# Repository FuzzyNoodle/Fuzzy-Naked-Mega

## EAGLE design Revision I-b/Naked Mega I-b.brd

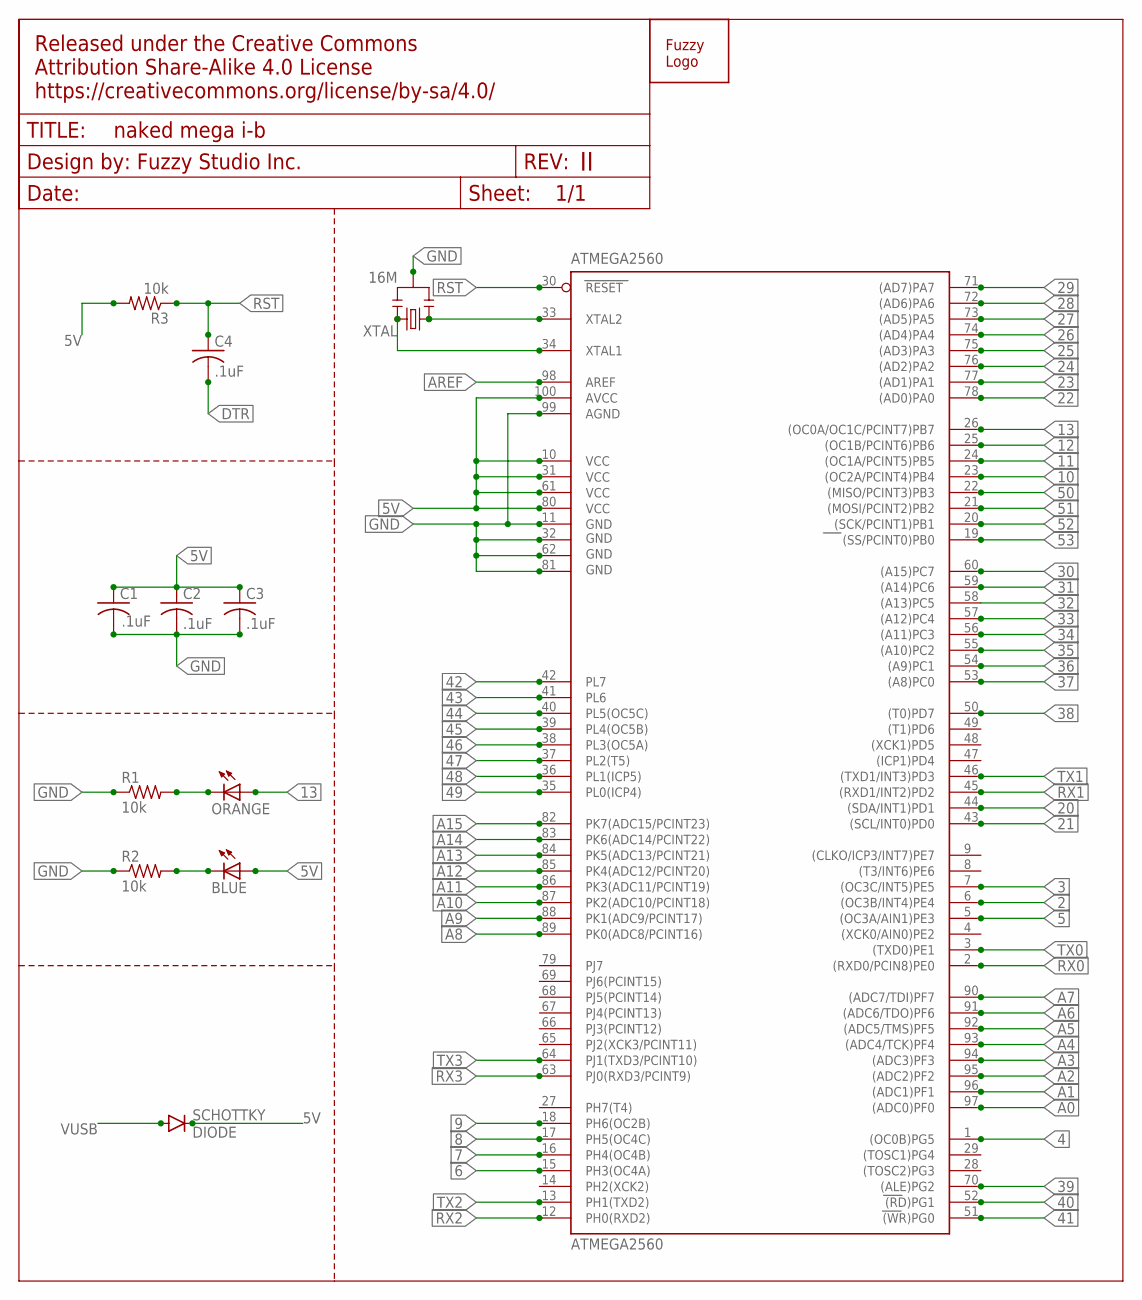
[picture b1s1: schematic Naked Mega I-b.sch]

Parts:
ATMEGA2560: ATMEGA2560; TQFP100
BLUE: L; SMD-0805-LED
C1: CAPACITOR-SMD-0805; SMD-0805
C2, C3, C4: .1uF; SMD-0805
ORANGE: L; SMD-0805-LED
R1, R2, R3: 10k; SMD-0805
SCHOTTKY: DIODE; SOD-323
U$1: LOGO; LOGO-S
U$3: DOCFRAME; CREATIVECOMMONS
XTAL: 16M; RESONATOR

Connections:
2: ATMEGA2560.6 ((OC3B/INT4)PE4)
3: ATMEGA2560.7 ((OC3C/INT5)PE5)
4: ATMEGA2560.1 ((OC0B)PG5)
5: ATMEGA2560.5 ((OC3A/AIN1)PE3)
5V: ATMEGA2560.10 (VCC), ATMEGA2560.31 (VCC1), ATMEGA2560.61 (VCC2), ATMEGA2560.80 (VCC3), ATMEGA2560.100 (AVCC), BLUE.1 (A), C1.1, C2.1, C3.1, R3.2, SCHOTTKY.C
6: ATMEGA2560.15 (PH3(OC4A))
7: ATMEGA2560.16 (PH4(OC4B))
8: ATMEGA2560.17 (PH5(OC4C))
9: ATMEGA2560.18 (PH6(OC2B))
10: ATMEGA2560.23 ((OC2A/PCINT4)PB4)
11: ATMEGA2560.24 ((OC1A/PCINT5)PB5)
12: ATMEGA2560.25 ((OC1B/PCINT6)PB6)
13: ATMEGA2560.26 ((OC0A/OC1C/PCINT7)PB7), ORANGE.1 (A)
20: ATMEGA2560.44 ((SDA/INT1)PD1)
21: ATMEGA2560.43 ((SCL/INT0)PD0)
22: ATMEGA2560.78 ((AD0)PA0)
23: ATMEGA2560.77 ((AD1)PA1)
24: ATMEGA2560.76 ((AD2)PA2)
25: ATMEGA2560.75 ((AD3)PA3)
26: ATMEGA2560.74 ((AD4)PA4)
27: ATMEGA2560.73 ((AD5)PA5)
28: ATMEGA2560.72 ((AD6)PA6)
29: ATMEGA2560.71 ((AD7)PA7)
30: ATMEGA2560.60 ((A15)PC7)
31: ATMEGA2560.59 ((A14)PC6)
32: ATMEGA2560.58 ((A13)PC5)
33: ATMEGA2560.57 ((A12)PC4)
34: ATMEGA2560.56 ((A11)PC3)
35: ATMEGA2560.55 ((A10)PC2)
36: ATMEGA2560.54 ((A9)PC1)
37: ATMEGA2560.53 ((A8)PC0)
38: ATMEGA2560.50 ((T0)PD7)
39: ATMEGA2560.70 ((ALE)PG2)
40: ATMEGA2560.52 ((RD)PG1)
41: ATMEGA2560.51 ((WR)PG0)
42: ATMEGA2560.42 (PL7)
43: ATMEGA2560.41 (PL6)
44: ATMEGA2560.40 (PL5(OC5C))
45: ATMEGA2560.39 (PL4(OC5B))
46: ATMEGA2560.38 (PL3(OC5A))
47: ATMEGA2560.37 (PL2(T5))
48: ATMEGA2560.36 (PL1(ICP5))
49: ATMEGA2560.35 (PL0(ICP4))
50: ATMEGA2560.22 ((MISO/PCINT3)PB3)
51: ATMEGA2560.21 ((MOSI/PCINT2)PB2)
52: ATMEGA2560.20 ((SCK/PCINT1)PB1)
53: ATMEGA2560.19 ((SS/PCINT0)PB0)
A0: ATMEGA2560.97 ((ADC0)PF0)
A1: ATMEGA2560.96 ((ADC1)PF1)
A2: ATMEGA2560.95 ((ADC2)PF2)
A3: ATMEGA2560.94 ((ADC3)PF3)
A4: ATMEGA2560.93 ((ADC4/TCK)PF4)
A5: ATMEGA2560.92 ((ADC5/TMS)PF5)
A6: ATMEGA2560.91 ((ADC6/TDO)PF6)
A7: ATMEGA2560.90 ((ADC7/TDI)PF7)
A8: ATMEGA2560.89 (PK0(ADC8/PCINT16))
A9: ATMEGA2560.88 (PK1(ADC9/PCINT17))
A10: ATMEGA2560.87 (PK2(ADC10/PCINT18))
A11: ATMEGA2560.86 (PK3(ADC11/PCINT19))
A12: ATMEGA2560.85 (PK4(ADC12/PCINT20))
A13: ATMEGA2560.84 (PK5(ADC13/PCINT21))
A14: ATMEGA2560.83 (PK6(ADC14/PCINT22))
A15: ATMEGA2560.82 (PK7(ADC15/PCINT23))
AREF: ATMEGA2560.98 (AREF)
DTR: C4.2
GND: ATMEGA2560.11 (GND), ATMEGA2560.32 (GND1), ATMEGA2560.62 (GND2), ATMEGA2560.81 (GND3), ATMEGA2560.99 (AGND), C1.2, C2.2, C3.2, R1.1, R2.1, XTAL.2
unnamed: ATMEGA2560.34 (XTAL1), XTAL.3
unnamed: ATMEGA2560.33 (XTAL2), XTAL.1
unnamed: ORANGE.2 (C), R1.2
unnamed: BLUE.2 (C), R2.2
RST: ATMEGA2560.30 (RESET), C4.1, R3.1
RX0: ATMEGA2560.2 ((RXD0/PCIN8)PE0)
RX1: ATMEGA2560.45 ((RXD1/INT2)PD2)
RX2: ATMEGA2560.12 (PH0(RXD2))
RX3: ATMEGA2560.63 (PJ0(RXD3/PCINT9))
TX0: ATMEGA2560.3 ((TXD0)PE1)
TX1: ATMEGA2560.46 ((TXD1/INT3)PD3)
TX2: ATMEGA2560.13 (PH1(TXD2))
TX3: ATMEGA2560.64 (PJ1(TXD3/PCINT10))
VUSB: SCHOTTKY.A

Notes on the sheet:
.1uF

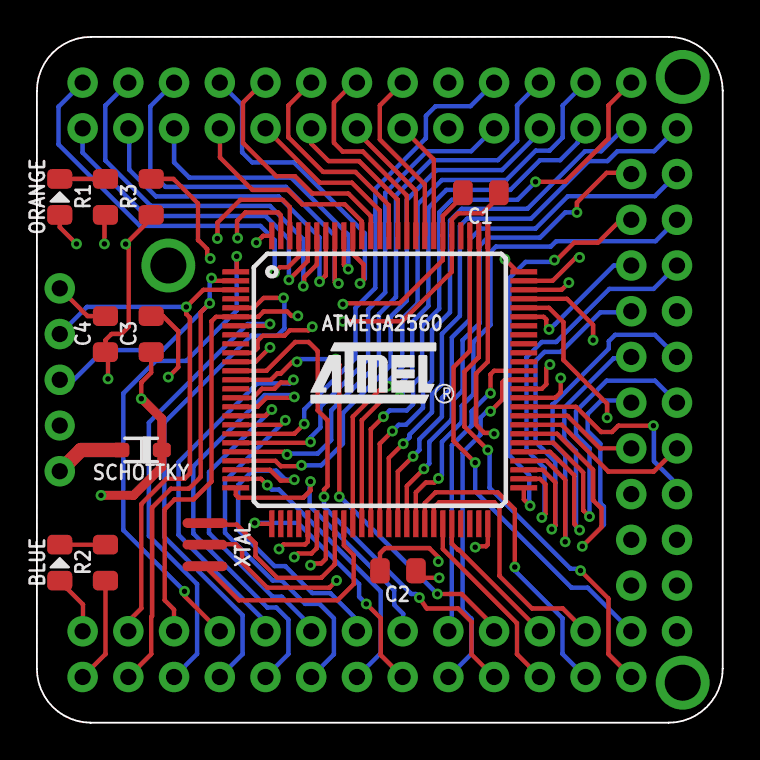
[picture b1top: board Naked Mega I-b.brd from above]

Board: 4 copper layers, 38.1 x 38.1 mm, 14 parts (1 on the bottom side), 8 nets.

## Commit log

2017-08-14 Testing
2017-11-13 Added Eagle library
2017-11-13 Eagle Library
2017-12-09 fixed error in line161
2017-12-09 Removed duplicate files
2019-01-21 Uplaod diptrace schematic and PCB files for Fuzzy Naked Mega 2

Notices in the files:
parts and their libraries:
Fuzzy: Released under the Creative Commons Attribution Share-Alike 4.0 License
Fuzzy: https://creativecommons.org/licenses/by-sa/4.0
Fuzzy: Released under the Creative Commons
Attribution Share-Alike 4.0 License
https://creativecommons.org/license/by-sa/4.0
